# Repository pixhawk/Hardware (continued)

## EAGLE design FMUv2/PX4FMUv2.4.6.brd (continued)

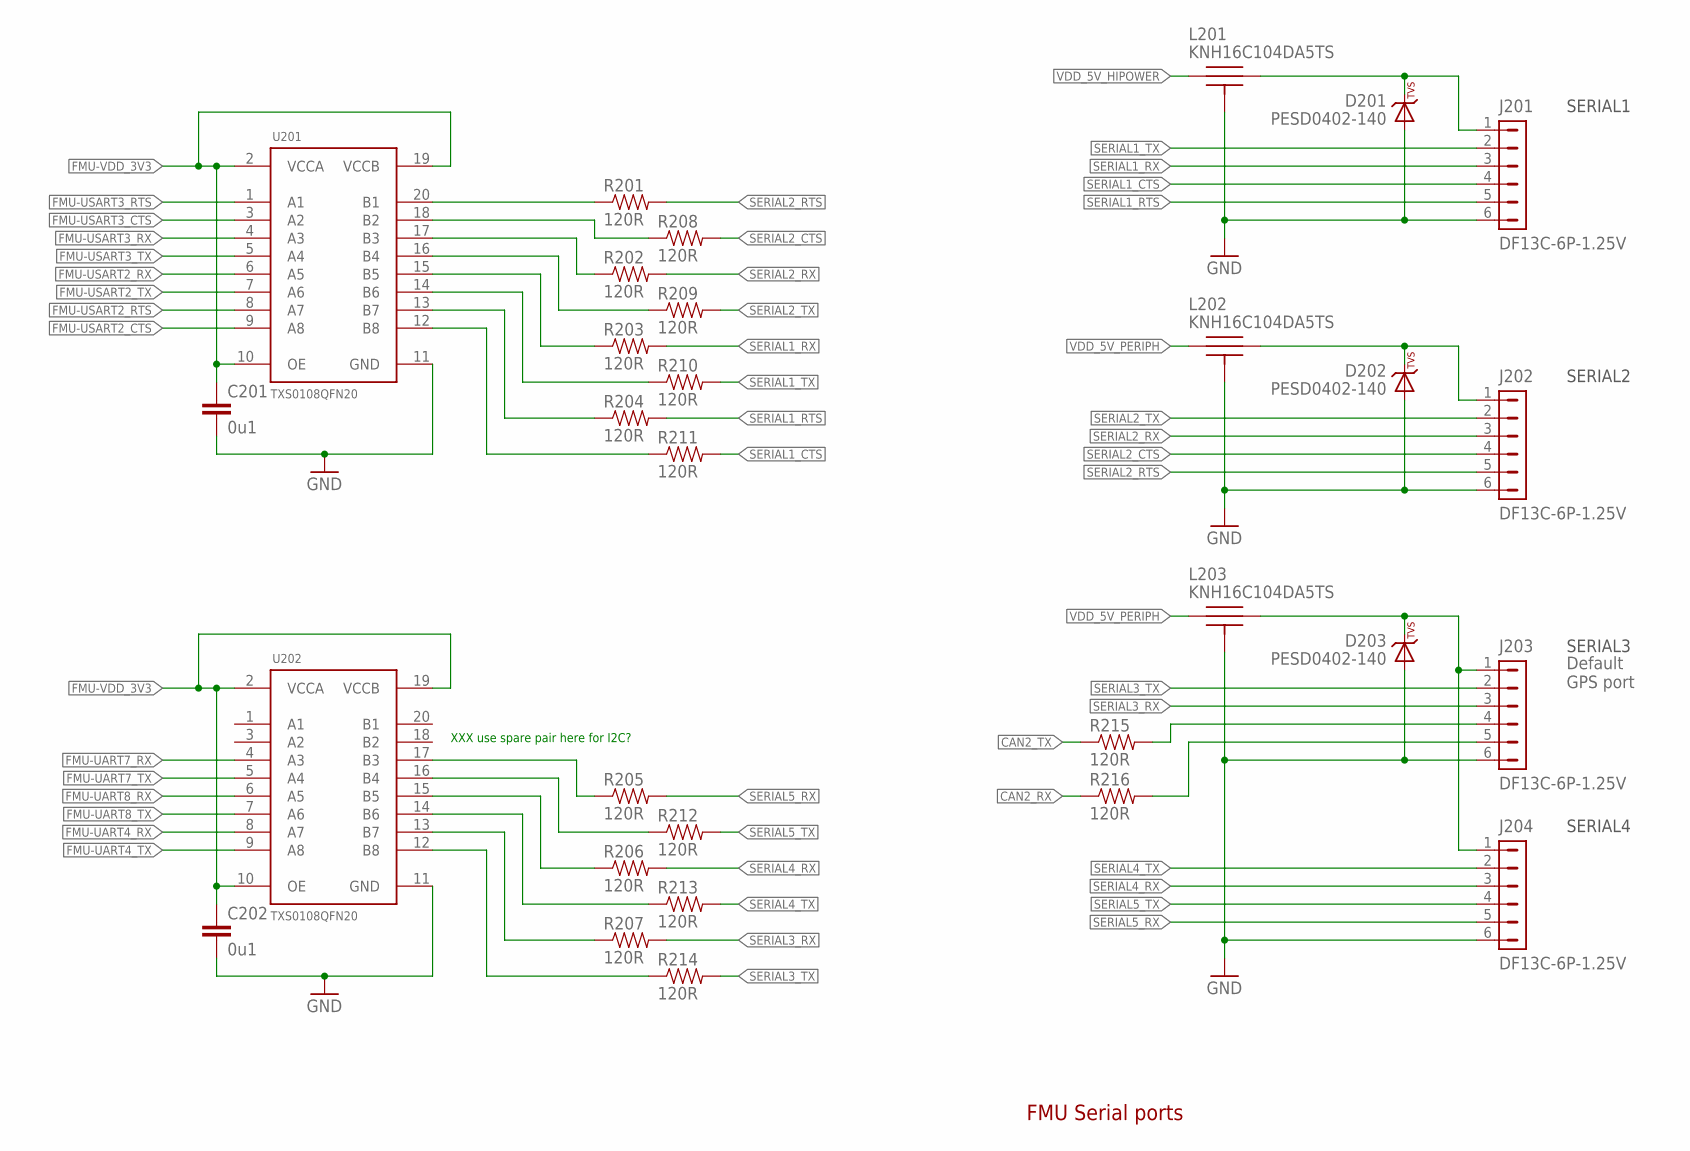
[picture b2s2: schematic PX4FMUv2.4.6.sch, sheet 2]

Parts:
C201, C202: 0u1; 0402-CAP; PARTNO CC0402ZRY5V7BB104
D201, D202, D203: PESD0402-140; 0402-TVS; PARTNO PESD0402-140
J201, J202, J203, J204: DF13C-6P-1.25V; PARTNO DF13C-6P-1.25V(20)
L201, L202, L203: KNH16C104DA5TS; KYOCERA-KNH16-DA; PARTNO KNH16C104DA5TS
R201, R202, R203, R204, R205, R206, R207, R208, R209, R210, R211, R212, R213, R214, R215, R216: 120R; 0402-RES; PARTNO RC0402FR-07120RL
U201, U202: TXS0108QFN20; QFN20-RGY; PARTNO TXS0108ERGYR

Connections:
CAN2_RX: R216.P$1 (1); also elsewhere on the board
CAN2_TX: R215.P$1 (1); also elsewhere on the board
FMU-UART4_RX: U202.8 (A7); also elsewhere on the board
FMU-UART4_TX: U202.9 (A8); also elsewhere on the board
FMU-UART7_RX: U202.4 (A3); also elsewhere on the board
FMU-UART7_TX: U202.5 (A4); also elsewhere on the board
FMU-UART8_RX: U202.6 (A5); also elsewhere on the board
FMU-UART8_TX: U202.7 (A6); also elsewhere on the board
FMU-USART2_CTS: U201.9 (A8); also elsewhere on the board
FMU-USART2_RTS: U201.8 (A7); also elsewhere on the board
FMU-USART2_RX: U201.6 (A5); also elsewhere on the board
FMU-USART2_TX: U201.7 (A6); also elsewhere on the board
FMU-USART3_CTS: U201.3 (A2); also elsewhere on the board
FMU-USART3_RTS: U201.1 (A1); also elsewhere on the board
FMU-USART3_RX: U201.4 (A3); also elsewhere on the board
FMU-USART3_TX: U201.5 (A4); also elsewhere on the board
FMU-VDD_3V3: C201.P$1 (1), C202.P$1 (1), U201.2 (VCCA), U201.10 (OE), U201.19 (VCCB), U202.2 (VCCA), U202.10 (OE), U202.19 (VCCB); also elsewhere on the board
GND: C201.P$2 (2), C202.P$2 (2), D201.A, D202.A, D203.A, J201.6, J202.6, J203.6, J204.6, L201.P$3, L201.P$4, L201.P$5, L202.P$3, L202.P$4, L202.P$5, L203.P$3, L203.P$4, L203.P$5, U201.11 (GND), U202.11 (GND); also elsewhere on the board
unnamed: D201.C, J201.1, L201.P$2
unnamed: J203.4, R215.P$2 (2)
unnamed: J203.5, R216.P$2 (2)
unnamed: R201.P$1 (1), U201.20 (B1)
unnamed: R208.P$1 (1), U201.18 (B2)
unnamed: R202.P$1 (1), U201.17 (B3)
unnamed: R209.P$1 (1), U201.16 (B4)
unnamed: R203.P$1 (1), U201.15 (B5)
unnamed: R210.P$1 (1), U201.14 (B6)
unnamed: R204.P$1 (1), U201.13 (B7)
unnamed: R211.P$1 (1), U201.12 (B8)
unnamed: R207.P$1 (1), U202.13 (B7)
unnamed: R214.P$1 (1), U202.12 (B8)
unnamed: R205.P$1 (1), U202.17 (B3)
unnamed: R212.P$1 (1), U202.16 (B4)
unnamed: R206.P$1 (1), U202.15 (B5)
unnamed: R213.P$1 (1), U202.14 (B6)
unnamed: D203.C, J203.1, J204.1, L203.P$2
unnamed: D202.C, J202.1, L202.P$2
SERIAL1_CTS: J201.4, R211.P$2 (2)
SERIAL1_RTS: J201.5, R204.P$2 (2)
SERIAL1_RX: J201.3, R203.P$2 (2); also elsewhere on the board
SERIAL1_TX: J201.2, R210.P$2 (2); also elsewhere on the board
SERIAL2_CTS: J202.4, R208.P$2 (2)
SERIAL2_RTS: J202.5, R201.P$2 (2)
SERIAL2_RX: J202.3, R202.P$2 (2); also elsewhere on the board
SERIAL2_TX: J202.2, R209.P$2 (2); also elsewhere on the board
SERIAL3_RX: J203.3, R207.P$2 (2); also elsewhere on the board
SERIAL3_TX: J203.2, R214.P$2 (2); also elsewhere on the board
SERIAL4_RX: J204.3, R206.P$2 (2); also elsewhere on the board
SERIAL4_TX: J204.2, R213.P$2 (2); also elsewhere on the board
SERIAL5_RX: J204.5, R205.P$2 (2); also elsewhere on the board
SERIAL5_TX: J204.4, R212.P$2 (2); also elsewhere on the board
VDD_5V_HIPOWER: L201.P$1; also elsewhere on the board
VDD_5V_PERIPH: L202.P$1, L203.P$1; also elsewhere on the board

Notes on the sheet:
FMU Serial ports
XXX use spare pair here for I2C?
SERIAL2
SERIAL1
SERIAL3
SERIAL4
Default GPS port

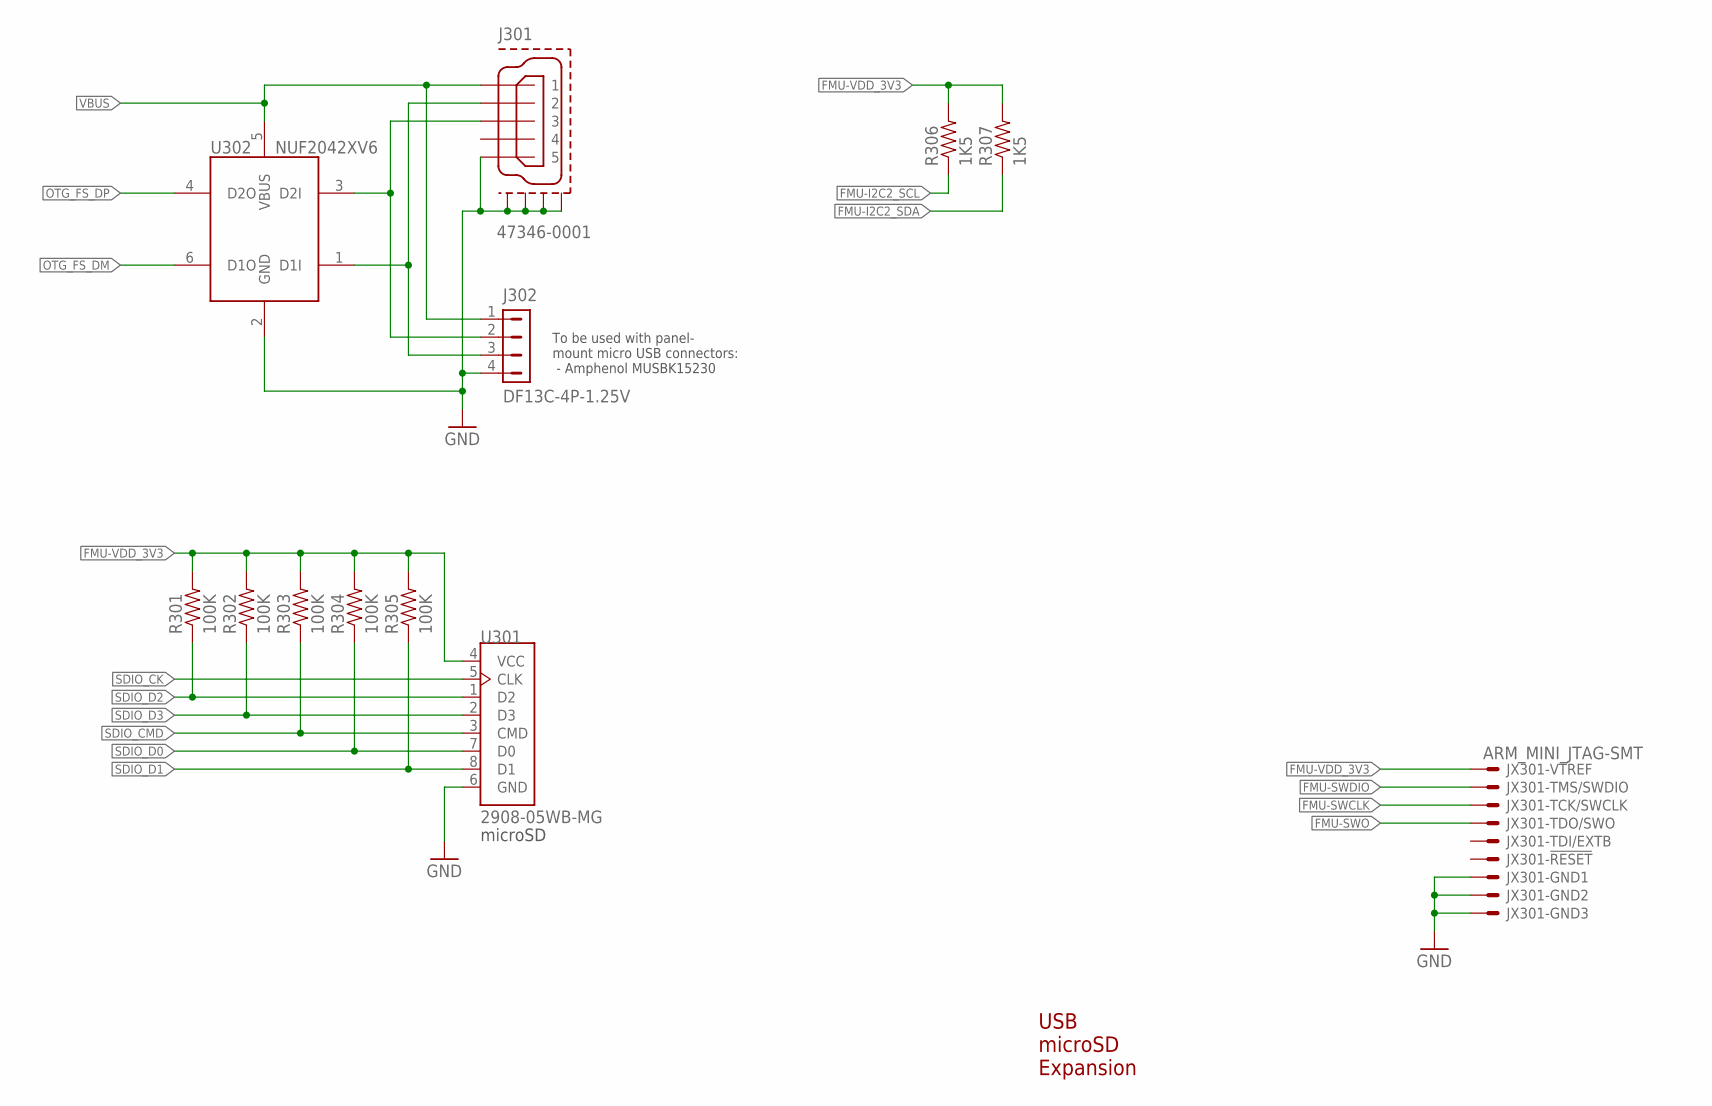
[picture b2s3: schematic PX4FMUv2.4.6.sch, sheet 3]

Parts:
J301: 47346-0001; MOLEX-47346-0001; PARTNO 47346-0001
J302: DF13C-4P-1.25V; PARTNO DF13C-4P-1.25V(20)
JX301: ARM_MINI_JTAG-SMT; FTSH-105-01-XXX-DV-K; PARTNO M50-3900542
R301, R302, R303, R304, R305: 100K; 0402-RES; PARTNO RC0402FR-07100KL
R306, R307: 1K5; 0402-RES; PARTNO RC0402FR-071K5L
U301: 2908-05WB-MG; MICROSD; PARTNO 2908-05WB-MG
U302: NUF2042XV6; SOT563-6; PARTNO NUF2042XV6T1G

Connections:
FMU-I2C2_SCL: R306.P$1 (1); also elsewhere on the board
FMU-I2C2_SDA: R307.P$1 (1); also elsewhere on the board
FMU-SWCLK: JX301.4; also elsewhere on the board
FMU-SWDIO: JX301.2; also elsewhere on the board
FMU-SWO: JX301.6; also elsewhere on the board
FMU-VDD_3V3: JX301.1, R301.P$2 (2), R302.P$2 (2), R303.P$2 (2), R304.P$2 (2), R305.P$2 (2), R306.P$2 (2), R307.P$2 (2), U301.4 (VCC); also elsewhere on the board
GND: J301.GND (5), J301.GND1, J301.GND2, J301.GND3, J301.GND4, J302.4, JX301.3, JX301.5, JX301.9, U301.6 (GND), U302.2 (GND); also elsewhere on the board
OTG_DM1: J301.D- (2), J302.3, U302.1 (D1I)
OTG_DP1: J301.D+ (3), J302.2, U302.3 (D2I)
OTG_FS_DM: U302.6 (D1O); also elsewhere on the board
OTG_FS_DP: U302.4 (D2O); also elsewhere on the board
SDIO_CK: U301.5 (CLK); also elsewhere on the board
SDIO_CMD: R303.P$1 (1), U301.3 (CMD); also elsewhere on the board
SDIO_D0: R304.P$1 (1), U301.7 (D0); also elsewhere on the board
SDIO_D1: R305.P$1 (1), U301.8 (D1); also elsewhere on the board
SDIO_D2: R301.P$1 (1), U301.1 (D2); also elsewhere on the board
SDIO_D3: R302.P$1 (1), U301.2 (D3); also elsewhere on the board
VBUS: J301.VBUS (1), J302.1, U302.5 (VBUS); also elsewhere on the board

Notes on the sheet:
USB microSD Expansion
microSD
To be used with panel- mount micro USB connectors: - Amphenol MUSBK15230

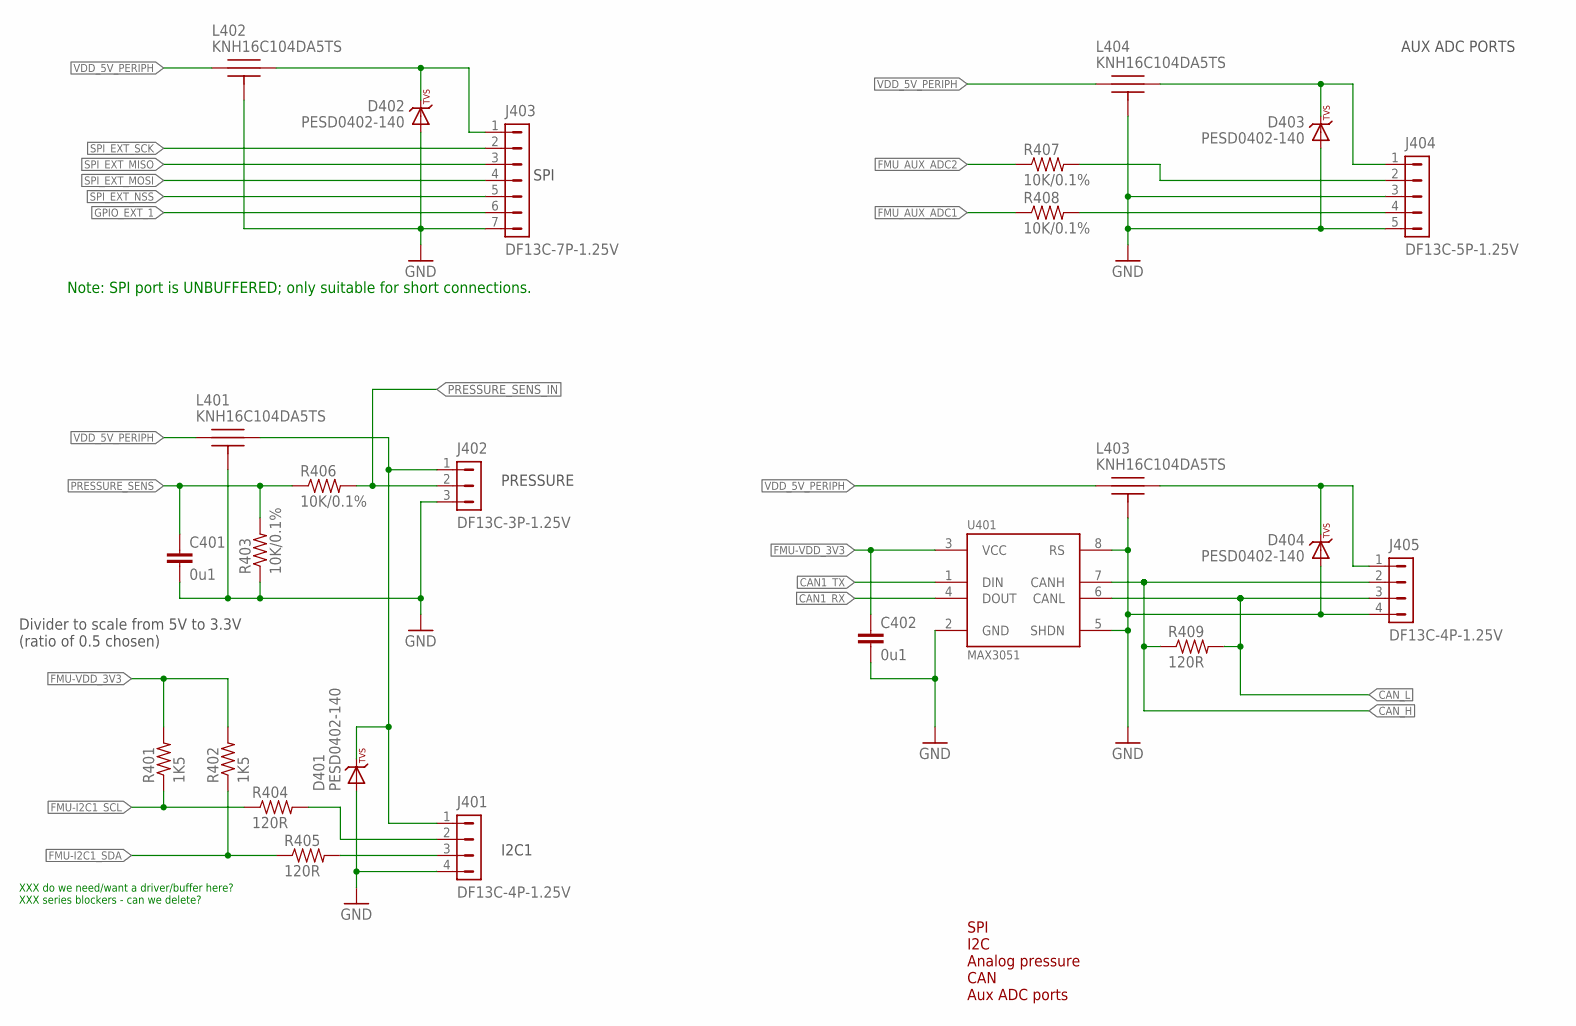
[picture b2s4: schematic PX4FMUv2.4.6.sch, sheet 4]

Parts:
C401, C402: 0u1; 0402-CAP; PARTNO CC0402ZRY5V7BB104
D401, D402, D403, D404: PESD0402-140; 0402-TVS; PARTNO PESD0402-140
J401, J405: DF13C-4P-1.25V; PARTNO DF13C-4P-1.25V(20)
J402: DF13C-3P-1.25V; PARTNO DF13C-3P-1.25V(20)
J403: DF13C-7P-1.25V; PARTNO DF13C-7P-1.25V(20)
J404: DF13C-5P-1.25V; PARTNO DF13C-5P-1.25V(20)
L401, L402, L403, L404: KNH16C104DA5TS; KYOCERA-KNH16-DA; PARTNO KNH16C104DA5TS
R401, R402: 1K5; 0402-RES; PARTNO RC0402FR-071K5L
R403, R406, R407, R408: 10K/0.1%; 0402-RES; PARTNO ERA-2AEB103X
R404, R405, R409: 120R; 0402-RES; PARTNO RC0402FR-07120RL
U401: MAX3051; SOT23-8; PARTNO MAX3051EKA

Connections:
!SPI_EXT_NSS: J403.5; also elsewhere on the board
CAN1_RX: U401.4 (DOUT); also elsewhere on the board
CAN1_TX: U401.1 (DIN); also elsewhere on the board
CAN_H: J405.2, R409.P$1 (1), U401.7 (CANH); also elsewhere on the board
CAN_L: J405.3, R409.P$2 (2), U401.6 (CANL); also elsewhere on the board
FMU-I2C1_SCL: R401.P$1 (1), R404.P$1 (1); also elsewhere on the board
FMU-I2C1_SDA: R402.P$1 (1), R405.P$1 (1); also elsewhere on the board
FMU-VDD_3V3: C402.P$1 (1), R401.P$2 (2), R402.P$2 (2), U401.3 (VCC); also elsewhere on the board
FMU_AUX_ADC1: R408.P$1 (1); also elsewhere on the board
FMU_AUX_ADC1_PROT: J404.4, R408.P$2 (2)
FMU_AUX_ADC2: R407.P$1 (1); also elsewhere on the board
FMU_AUX_ADC2_PROT: J404.2, R407.P$2 (2)
GND: C401.P$2 (2), C402.P$2 (2), D401.A, D402.A, D403.A, D404.A, J401.4, J402.3, J403.7, J404.3, J404.5, J405.4, L401.P$3, L401.P$4, L401.P$5, L402.P$3, L402.P$4, L402.P$5, L403.P$3, L403.P$4, L403.P$5, L404.P$3, L404.P$4, L404.P$5, R403.P$1 (1), U401.2 (GND), U401.5 (SHDN), U401.8 (RS); also elsewhere on the board
GPIO_EXT_1: J403.6; also elsewhere on the board
unnamed: J401.2, R404.P$2 (2)
unnamed: J401.3, R405.P$2 (2)
unnamed: D402.C, J403.1, L402.P$2
unnamed: D401.C, J401.1, J402.1, L401.P$2
unnamed: D404.C, J405.1, L403.P$2
unnamed: D403.C, J404.1, L404.P$2
PRESSURE_SENS: C401.P$1 (1), R403.P$2 (2), R406.P$1 (1); also elsewhere on the board
PRESSURE_SENS_IN: J402.2, R406.P$2 (2); also elsewhere on the board
SPI_EXT_MISO: J403.3; also elsewhere on the board
SPI_EXT_MOSI: J403.4; also elsewhere on the board
SPI_EXT_SCK: J403.2; also elsewhere on the board
VDD_5V_PERIPH: L401.P$1, L402.P$1, L403.P$1, L404.P$1; also elsewhere on the board

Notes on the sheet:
SPI
PRESSURE
XXX do we need/want a driver/buffer here? XXX series blockers - can we delete?
I2C1
AUX ADC PORTS
SPI I2C Analog pressure CAN Aux ADC ports
Note: SPI port is UNBUFFERED; only suitable for short connections.
Divider to scale from 5V to 3.3V (ratio of 0.5 chosen)

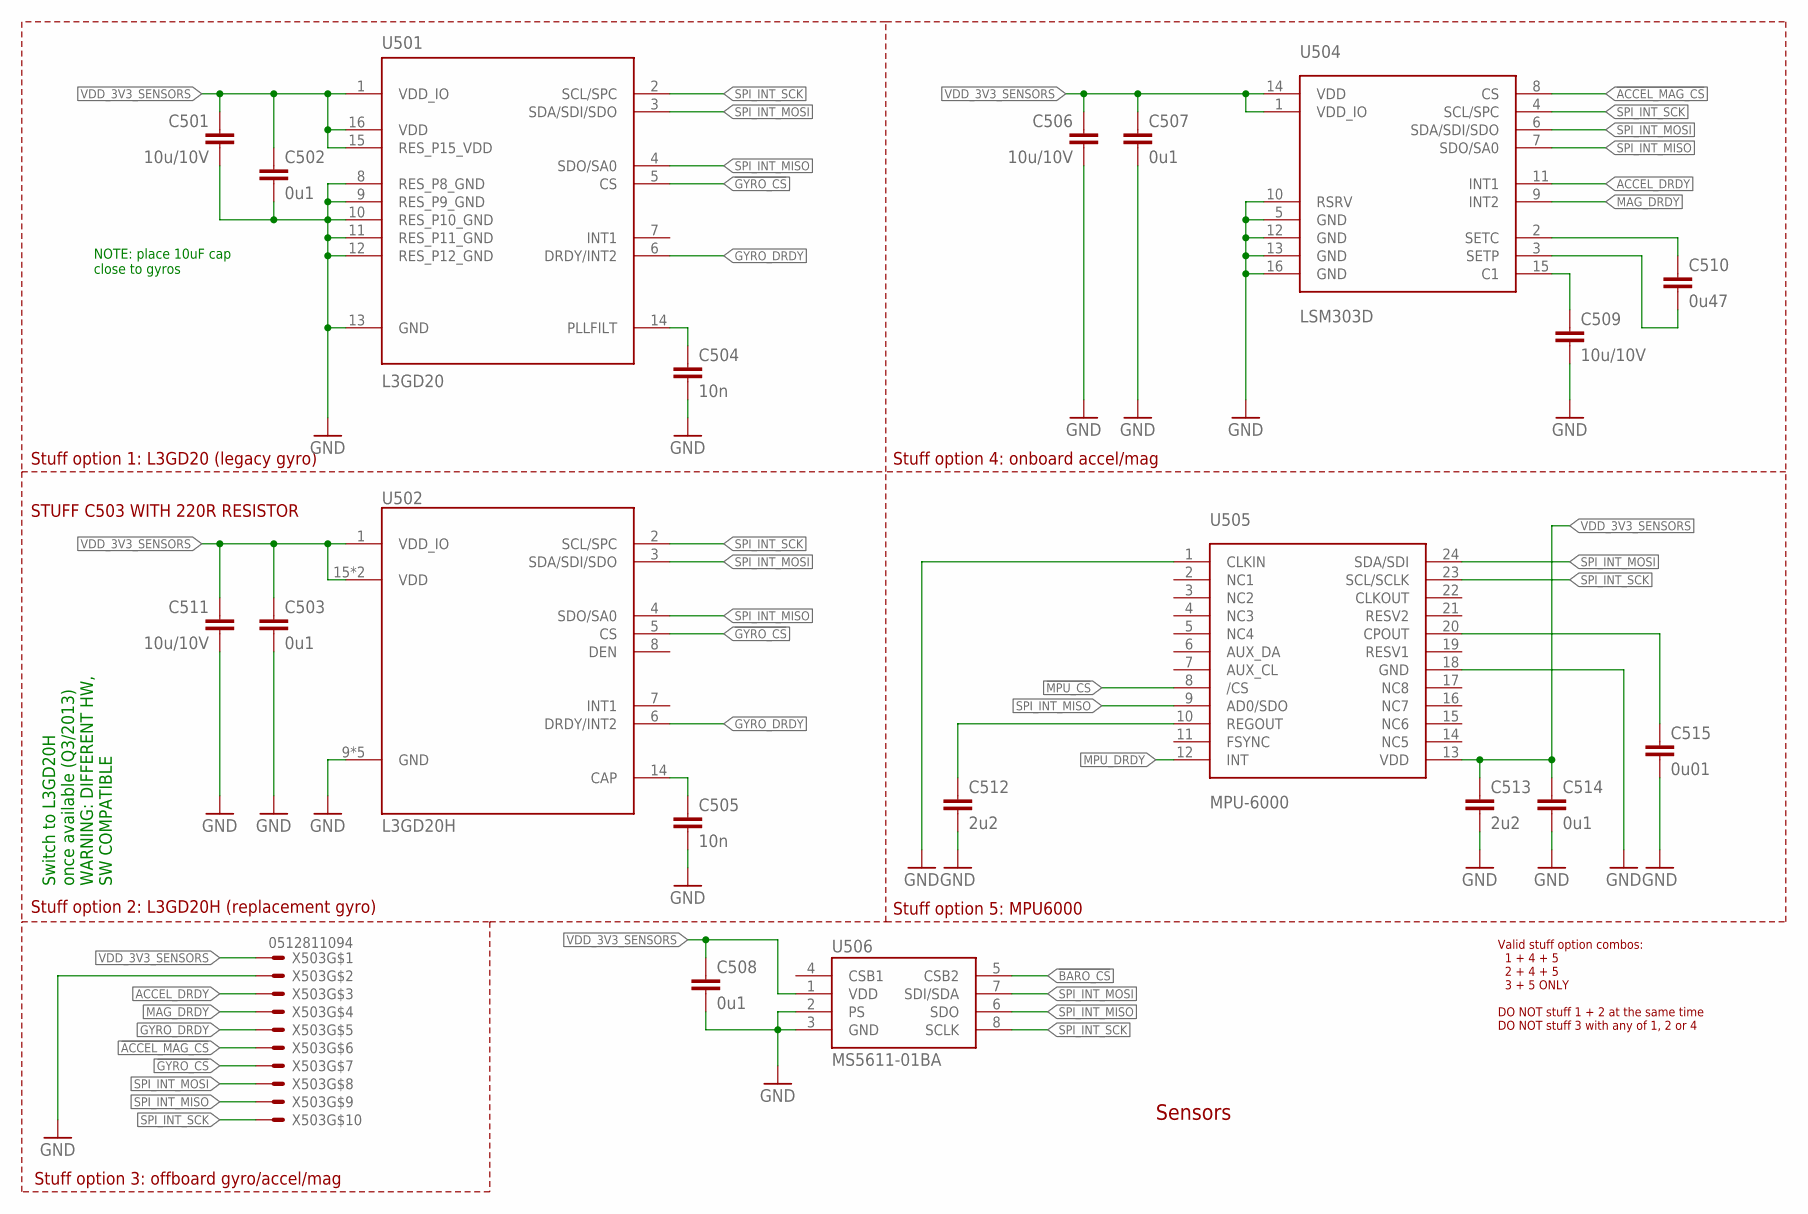
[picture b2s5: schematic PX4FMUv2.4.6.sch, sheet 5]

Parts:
C501, C506, C509, C511: 10u/10V; 0805-CAP; PARTNO CC0805ZKY5V6BB106
C502, C503, C507, C508, C514: 0u1; 0402-CAP; PARTNO CC0402ZRY5V7BB104
C504, C505: 10n; 0402-CAP; PARTNO CC0402KRX7R7BB103
C510: 0u47; 0402-CAP; PARTNO C1005X5R1C474K050BC
C512, C513: 2u2; 0603-CAP; PARTNO C1608X6S1C225K080AC
C515: 0u01; 0603-CAP; PARTNO 06033C103JAT2A
U501: L3GD20; L3G4200DH-MAN; PARTNO L3GD20
U502: L3GD20H; LGA-16L; PARTNO L3GD20H
U504: LSM303D; LGA-16L; PARTNO LSM303D
U505: MPU-6000; QFN-24; PARTNO MPU-6000
U506: MS5611-01BA; PARTNO MS5611-01BA
X503: 0512811094; 51281-1094; PARTNO 0781191109

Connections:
!ACCEL_MAG_CS: U504.8 (CS), X503.6; also elsewhere on the board
!BARO_CS: U506.5 (CSB2); also elsewhere on the board
!GYRO_CS: U501.5 (CS), U502.5 (CS), X503.7; also elsewhere on the board
!MPU_CS: U505.8 (/CS); also elsewhere on the board
ACCEL_DRDY: U504.11 (INT1), X503.3; also elsewhere on the board
GND: C501.P$2 (2), C502.P$2 (2), C503.P$2 (2), C504.P$2 (2), C505.P$2 (2), C506.P$2 (2), C507.P$2 (2), C508.P$2 (2), C509.P$2 (2), C511.P$2 (2), C512.P$2 (2), C513.P$2 (2), C514.P$2 (2), C515.P$2 (2), U501.8 (RES_P8_GND), U501.9 (RES_P9_GND), U501.10 (RES_P10_GND), U501.11 (RES_P11_GND), U501.12 (RES_P12_GND), U501.13 (GND), U502.9 (GND), U502.10 (GND), U502.11 (GND), U502.12 (GND), U502.13 (GND), U504.5 (GND), U504.10 (RSRV), U504.12 (GND), U504.13 (GND), U504.16 (GND), U505.1 (CLKIN), U505.18 (GND), U506.2 (PS), U506.3 (GND), X503.2; also elsewhere on the board
GYRO_DRDY: U501.6 (DRDY/INT2), U502.6 (DRDY/INT2), X503.5; also elsewhere on the board
MAG_DRDY: U504.9 (INT2), X503.4; also elsewhere on the board
MPU_DRDY: U505.12 (INT); also elsewhere on the board
unnamed: C509.P$1 (1), U504.15 (C1)
unnamed: C510.P$1 (1), U504.2 (SETC)
unnamed: C510.P$2 (2), U504.3 (SETP)
unnamed: C505.P$1 (1), U502.14 (CAP)
unnamed: C504.P$1 (1), U501.14 (PLLFILT)
unnamed: C512.P$1 (1), U505.10 (REGOUT)
unnamed: C515.P$1 (1), U505.20 (CPOUT)
SPI_INT_MISO: U501.4 (SDO/SA0), U502.4 (SDO/SA0), U504.7 (SDO/SA0), U505.9 (AD0/SDO), U506.6 (SDO), X503.9; also elsewhere on the board
SPI_INT_MOSI: U501.3 (SDA/SDI/SDO), U502.3 (SDA/SDI/SDO), U504.6 (SDA/SDI/SDO), U505.24 (SDA/SDI), U506.7 (SDI/SDA), X503.8; also elsewhere on the board
SPI_INT_SCK: U501.2 (SCL/SPC), U502.2 (SCL/SPC), U504.4 (SCL/SPC), U505.23 (SCL/SCLK), U506.8 (SCLK), X503.10; also elsewhere on the board
VDD_3V3_SENSORS: C501.P$1 (1), C502.P$1 (1), C503.P$1 (1), C506.P$1 (1), C507.P$1 (1), C508.P$1 (1), C511.P$1 (1), C513.P$1 (1), C514.P$1 (1), U501.1 (VDD_IO), U501.15 (RES_P15_VDD), U501.16 (VDD), U502.1 (VDD_IO), U502.15 (VDD), U502.16 (VDD), U504.1 (VDD_IO), U504.14 (VDD), U505.13 (VDD), U506.1 (VDD), X503.1; also elsewhere on the board

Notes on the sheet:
Sensors
Switch to L3GD20H once available (Q3/2013) WARNING: DIFFERENT HW, SW COMPATIBLE
NOTE: place 10uF cap close to gyros
Stuff option 1: L3GD20 (legacy gyro)
Stuff option 2: L3GD20H (replacement gyro)
Stuff option 4: onboard accel/mag
Valid stuff option combos: 1 + 4 + 5 2 + 4 + 5 3 + 5 ONLY DO NOT stuff 1 + 2 at the same time DO NOT stuff 3 with any of 1, 2 or 4
Stuff option 5: MPU6000
Stuff option 3: offboard gyro/accel/mag
STUFF C503 WITH 220R RESISTOR

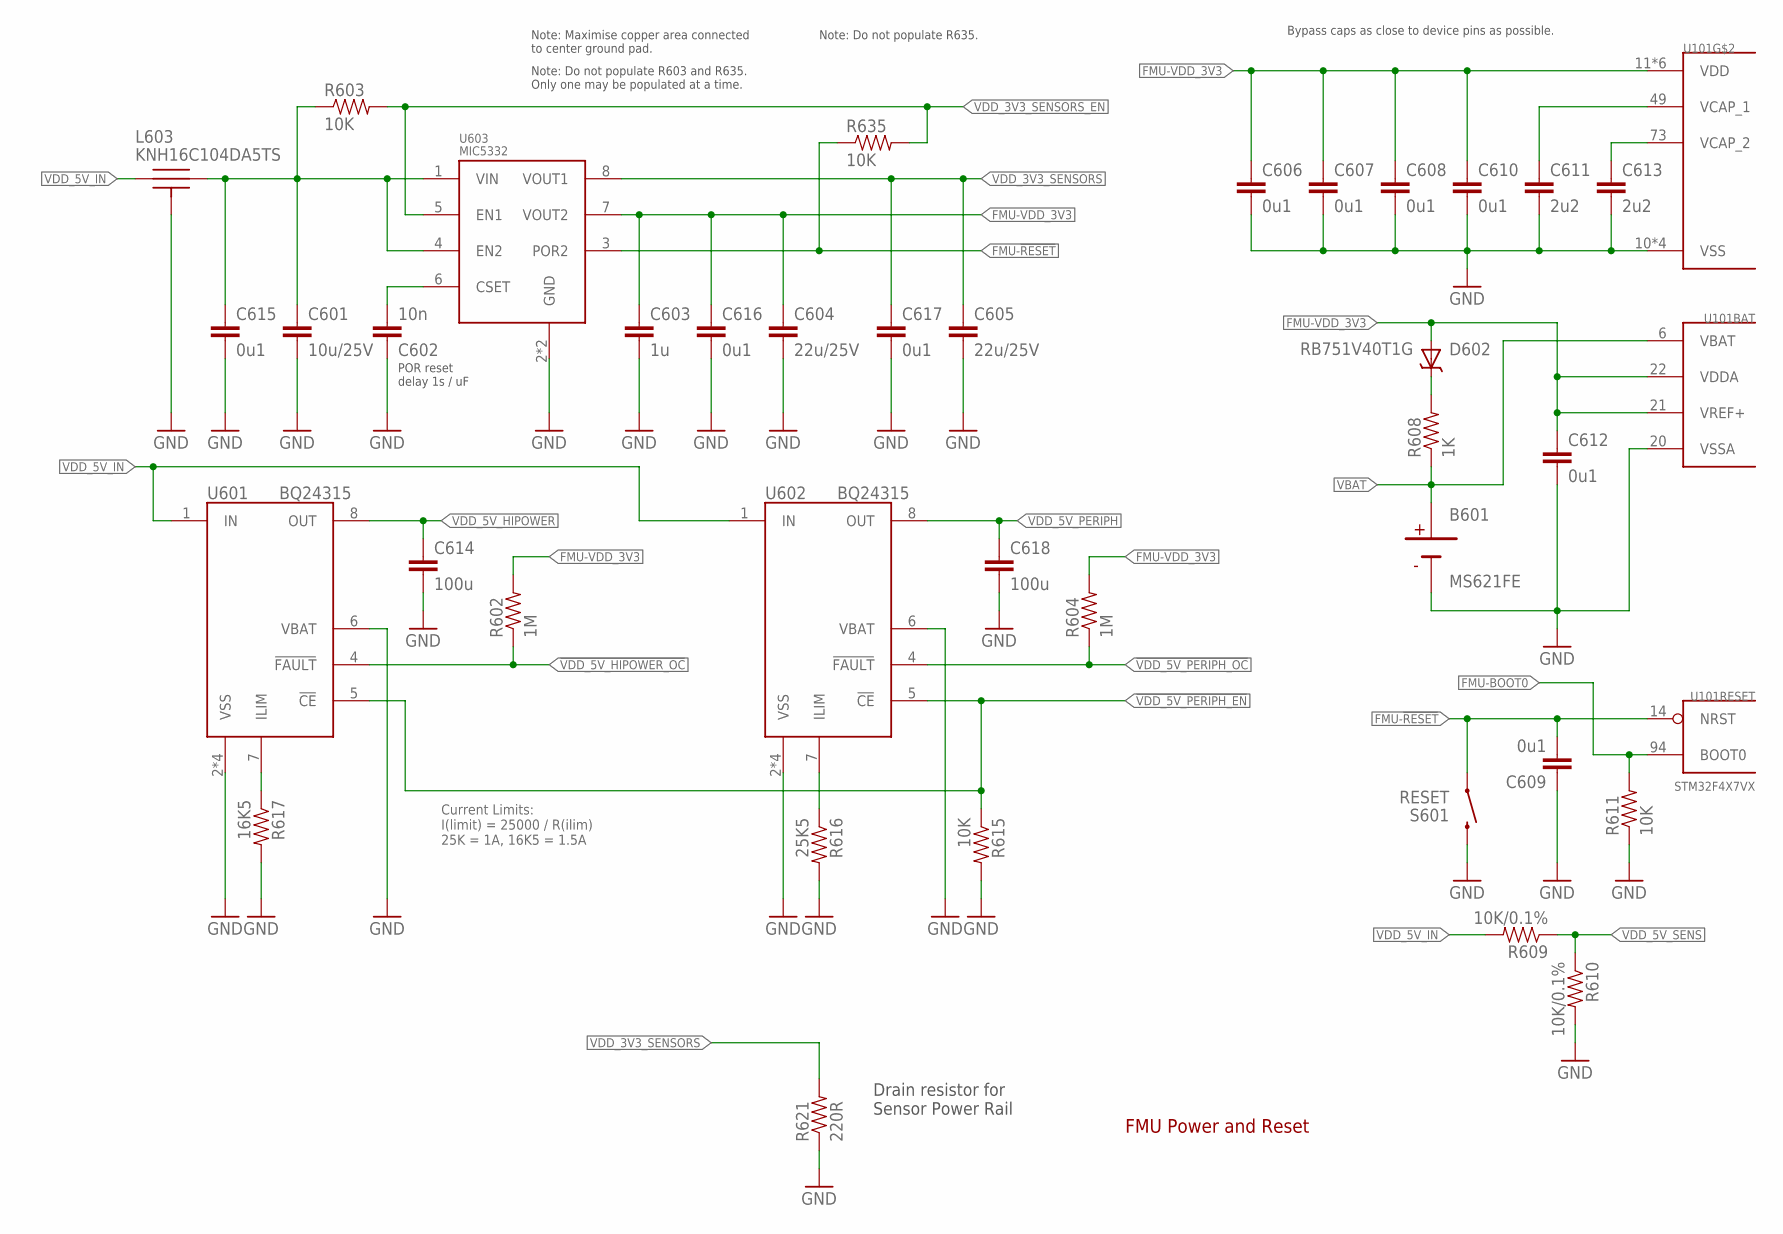
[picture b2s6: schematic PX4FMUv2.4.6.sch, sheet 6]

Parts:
B601: MS621FE; PARTNO MS621FE-FL11E
C601: 10u/25V; 0805-CAP; PARTNO CL21A106KAYNNNE
C602: 10n; 0402-CAP; PARTNO CC0402KRX7R7BB103
C603: 1u; 0603-CAP; PARTNO CC0603ZRY5V7BB105
C604, C605: 22u/25V; 0805-CAP; PARTNO CL21A226MAQNNNE
C606, C607, C608, C609, C610, C612, C615, C616, C617: 0u1; 0402-CAP; PARTNO CC0402ZRY5V7BB104
C611, C613: 2u2; 0603-CAP; PARTNO C1608X6S1C225K080AC
C614, C618: 100u; 1206-CAP; PARTNO C3216X5R1A107M160AC
D602: RB751V40T1G; SOD323; PARTNO RB751V40T1G
L603: KNH16C104DA5TS; KYOCERA-KNH16-DA; PARTNO KNH16C104DA5TS
R602, R604: 1M; 0402-RES; PARTNO RC0402FR-071ML
R603, R611, R615, R635: 10K; 0402-RES; PARTNO RC0402FR-0710KL
R608: 1K; 0402-RES; PARTNO RC0402FR-071KL
R609, R610: 10K/0.1%; 0402-RES; PARTNO ERA-2AEB103X
R616: 25K5; 0402-RES; PARTNO RMCF0402FT25K5
R617: 16K5; 0402-RES; PARTNO RMCF0402FT16K5
R621: 220R; 0603-RES; PARTNO RC1608J100CS
S601: RESET; EVQP7J01K; PARTNO EVQ-P7J01P
U101: STM32F4X7VX; TQFP100; PARTNO STM32F427VI
U601, U602: BQ24315; QFN8-DSG; PARTNO BQ24315DSGR
U603: MIC5332; MLF-8-EPAD; PARTNO MIC5332-SSYMT

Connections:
!VDD_5V_HIPOWER_OC: R602.P$1 (1), U601.4 (!FAULT); also elsewhere on the board
!VDD_5V_PERIPH_EN: R615.P$1 (1), U601.5 (!CE), U602.5 (!CE); also elsewhere on the board
!VDD_5V_PERIPH_OC: R604.P$1 (1), U602.4 (!FAULT); also elsewhere on the board
FMU-!RESET: C609.P$2 (2), R635.P$1 (1), S601.A1 (1), U101.14 (NRST), U603.3 (POR2); also elsewhere on the board
FMU-BOOT0: R611.P$2 (2), U101.94 (BOOT0); also elsewhere on the board
FMU-VDD_3V3: C603.P$1 (1), C604.P$1 (1), C606.P$1 (1), C607.P$1 (1), C608.P$1 (1), C610.P$1 (1), C612.P$1 (1), C616.P$1 (1), D602.A, R602.P$2 (2), R604.P$2 (2), U101.11 (VDD), U101.19 (VDD), U101.21 (VREF+), U101.22 (VDDA), U101.28 (VDD), U101.50 (VDD), U101.75 (VDD), U101.100 (VDD), U603.7 (VOUT2); also elsewhere on the board
FMU-VDD_5V5: C601.P$1 (1), C615.P$1 (1), L603.P$2, R603.P$1 (1), U603.1 (VIN), U603.4 (EN2)
GND: B601.2 (NEG), C601.P$2 (2), C602.P$1 (1), C603.P$2 (2), C604.P$2 (2), C605.P$2 (2), C606.P$2 (2), C607.P$2 (2), C608.P$2 (2), C609.P$1 (1), C610.P$2 (2), C611.P$2 (2), C612.P$2 (2), C613.P$2 (2), C614.P$2 (2), C615.P$2 (2), C616.P$2 (2), C617.P$2 (2), C618.P$2 (2), L603.P$3, L603.P$4, L603.P$5, R610.P$2 (2), R611.P$1 (1), R615.P$2 (2), R616.P$2 (2), R617.P$2 (2), R621.1, S601.B3 (2), U101.10 (VSS), U101.20 (VSSA), U101.27 (VSS), U101.74 (VSS), U101.99 (VSS), U601.2 (VSS), U601.6 (VBAT), U601.GND (VSS), U601.P$2 (VSS), U601.P$3 (VSS), U602.2 (VSS), U602.6 (VBAT), U602.GND (VSS), U602.P$2 (VSS), U602.P$3 (VSS), U603.2 (GND), U603.GND; also elsewhere on the board
unnamed: C613.P$1 (1), U101.73 (VCAP_2)
unnamed: C602.P$2 (2), U603.6 (CSET)
unnamed: C611.P$1 (1), U101.49 (VCAP_1)
unnamed: D602.C, R608.P$2 (2)
unnamed: R616.P$1 (1), U602.7 (ILIM)
unnamed: R617.P$1 (1), U601.7 (ILIM)
VBAT: B601.1 (POS), R608.P$1 (1), U101.6 (VBAT); also elsewhere on the board
VDD_3V3_SENSORS: C605.P$1 (1), C617.P$1 (1), R621.2, U603.8 (VOUT1); also elsewhere on the board
VDD_3V3_SENSORS_EN: R603.P$2 (2), R635.P$2 (2), U603.5 (EN1); also elsewhere on the board
VDD_5V_HIPOWER: C614.P$1 (1), U601.8 (OUT); also elsewhere on the board
VDD_5V_IN: L603.P$1, R609.P$2 (2), U601.1 (IN), U602.1 (IN); also elsewhere on the board
VDD_5V_PERIPH: C618.P$1 (1), U602.8 (OUT); also elsewhere on the board
VDD_5V_SENS: R609.P$1 (1), R610.P$1 (1); also elsewhere on the board

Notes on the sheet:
FMU Power and Reset
Bypass caps as close to device pins as possible.
Note: Maximise copper area connected to center ground pad.
POR reset delay 1s / uF
Current Limits: I(limit) = 25000 / R(ilim) 25K = 1A, 16K5 = 1.5A
Drain resistor for Sensor Power Rail
Note: Do not populate R603 and R635. Only one may be populated at a time.
Note: Do not populate R635.

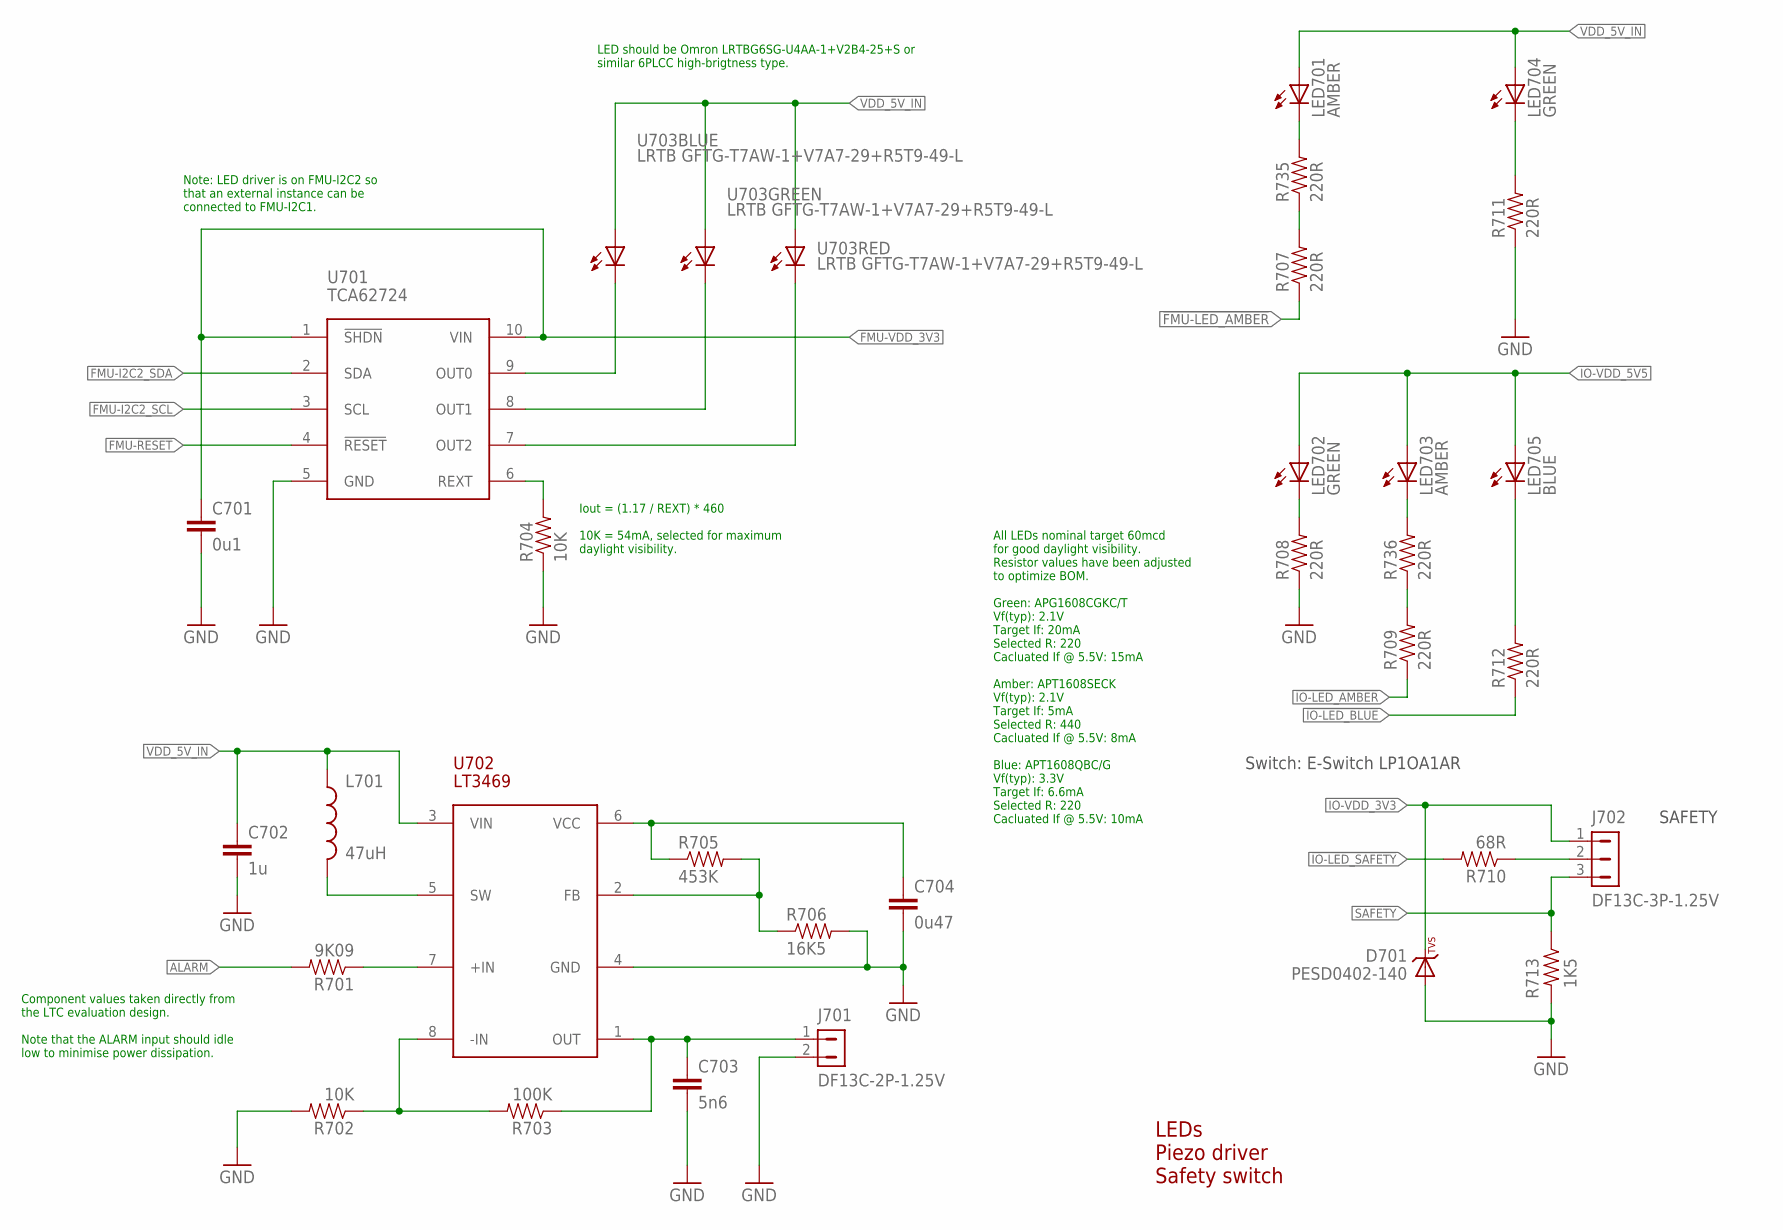
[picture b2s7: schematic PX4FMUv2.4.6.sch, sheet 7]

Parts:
C701: 0u1; 0402-CAP; PARTNO CC0402ZRY5V7BB104
C702: 1u; 0603-CAP; PARTNO CC0603ZRY5V7BB105
C703: 5n6; 0402-CAP; PARTNO C0402C562K5RACTU
C704: 0u47; 0402-CAP; PARTNO C1005X5R1C474K050BC
D701: PESD0402-140; 0402-TVS; PARTNO PESD0402-140
J701: DF13C-2P-1.25V; PARTNO DF13C-2P-1.25V(20)
J702: DF13C-3P-1.25V; PARTNO DF13C-3P-1.25V(20)
L701: 47uH; 0805-IND; PARTNO MLZ2012M470W
LED701, LED703: AMBER; 0603-LED; PARTNO APTD1608SECK
LED702, LED704: GREEN; 0603-LED; PARTNO APTD1608CGCK
LED705: BLUE; 0603-LED; PARTNO APTD1608QBC/D
R701: 9K09; 0402-RES; PARTNO RMCF0402FT9K09
R702, R704: 10K; 0402-RES; PARTNO RC0402FR-0710KL
R703: 100K; 0402-RES; PARTNO RC0402FR-07100KL
R705: 453K; 0402-RES; PARTNO RMCF0402FT453K
R706: 16K5; 0402-RES; PARTNO RMCF0402FT16K5
R707, R708, R709, R711, R712, R735, R736: 220R; 0402-RES; PARTNO RC0402FR-07220RL
R710: 68R; 0402-RES; PARTNO ERJ-2GEJ680X
R713: 1K5; 0402-RES; PARTNO RC0402FR-071K5L
U701: TCA62724FMG; SON10; PARTNO TCA62724FMG
U702: LT3469; SOT23-8; PARTNO LT3469ETS8
U703: LRTB GFTG-T7AW-1+V7A7-29+R5T9-49-L; 6-PLCC; PARTNO LRTB GFTG-T7AW-1+V7A7-29+R5T9-49-L

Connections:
!FMU-LED_AMBER: R707.P$1 (1); also elsewhere on the board
!IO-LED_AMBER: R709.P$1 (1); also elsewhere on the board
!IO-LED_BLUE: R712.P$1 (1); also elsewhere on the board
!IO-LED_SAFETY: R710.P$2 (2); also elsewhere on the board
ALARM: R701.P$2 (2); also elsewhere on the board
FMU-!RESET: U701.4 (!RESET); also elsewhere on the board
FMU-I2C2_SCL: U701.3 (SCL); also elsewhere on the board
FMU-I2C2_SDA: U701.2 (SDA); also elsewhere on the board
FMU-VDD_3V3: C701.P$1 (1), U701.1 (!SHDN), U701.10 (VIN); also elsewhere on the board
GND: C701.P$2 (2), C702.P$2 (2), C703.P$2 (2), C704.P$2 (2), D701.A, J701.2, R702.P$2 (2), R704.P$1 (1), R706.P$2 (2), R708.P$1 (1), R711.P$1 (1), R713.P$2 (2), U701.5 (GND), U702.4 (GND); also elsewhere on the board
IO-VDD_3V3: D701.C, J702.1; also elsewhere on the board
IO-VDD_5V5: LED702.A, LED703.A, LED705.A; also elsewhere on the board
unnamed: LED704.C, R711.P$2 (2)
unnamed: LED705.C, R712.P$2 (2)
unnamed: R707.P$2 (2), R735.P$1 (1)
unnamed: R705.P$2 (2), R706.P$1 (1), U702.2 (FB)
unnamed: R702.P$1 (1), R703.P$2 (2), U702.8 (-IN)
unnamed: LED701.C, R735.P$2 (2)
unnamed: C703.P$1 (1), J701.1, R703.P$1 (1), U702.1 (OUT)
unnamed: R701.P$1 (1), U702.7 (+IN)
unnamed: LED702.C, R708.P$2 (2)
unnamed: L701.P$2 (2), U702.5 (SW)
unnamed: C704.P$1 (1), R705.P$1 (1), U702.6 (VCC)
unnamed: R709.P$2 (2), R736.P$1 (1)
unnamed: LED703.C, R736.P$2 (2)
unnamed: J702.2, R710.P$1 (1)
unnamed: R704.P$2 (2), U701.6 (REXT)
RGB_LED_3: U701.9 (OUT0), U703.C1 (C)
RGB_LED_4: U701.8 (OUT1), U703.C2 (C)
RGB_LED_14: U701.7 (OUT2), U703.C3 (C)
SAFETY: J702.3, R713.P$1 (1); also elsewhere on the board
VDD_5V_IN: C702.P$1 (1), L701.P$1 (1), LED701.A, LED704.A, U702.3 (VIN), U703.A1 (A), U703.A2 (A), U703.A3 (A); also elsewhere on the board

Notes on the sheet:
LEDs Piezo driver Safety switch
Switch: E-Switch LP1OA1AR
SAFETY
LED should be Omron LRTBG6SG-U4AA-1+V2B4-25+S or similar 6PLCC high-brigtness type.
Iout = (1.17 / REXT) * 460 10K = 54mA, selected for maximum daylight visibility.
Note: LED driver is on FMU-I2C2 so that an external instance can be connected to FMU-I2C1.
All LEDs nominal target 60mcd for good daylight visibility. Resistor values have been adjusted to optimize BOM. Green: APG1608CGKC/T Vf(typ): 2.1V Target If: 20mA Selected R: 220 Cacluated If @ 5.5V: 15mA Amber: APT1608SECK Vf(typ): 2.1V Target If: 5mA Selected R: 440 Cacluated If @ 5.5V: 8mA Blue: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
Component values taken directly from the LTC evaluation design. Note that the ALARM input should idle low to minimise power dissipation.
